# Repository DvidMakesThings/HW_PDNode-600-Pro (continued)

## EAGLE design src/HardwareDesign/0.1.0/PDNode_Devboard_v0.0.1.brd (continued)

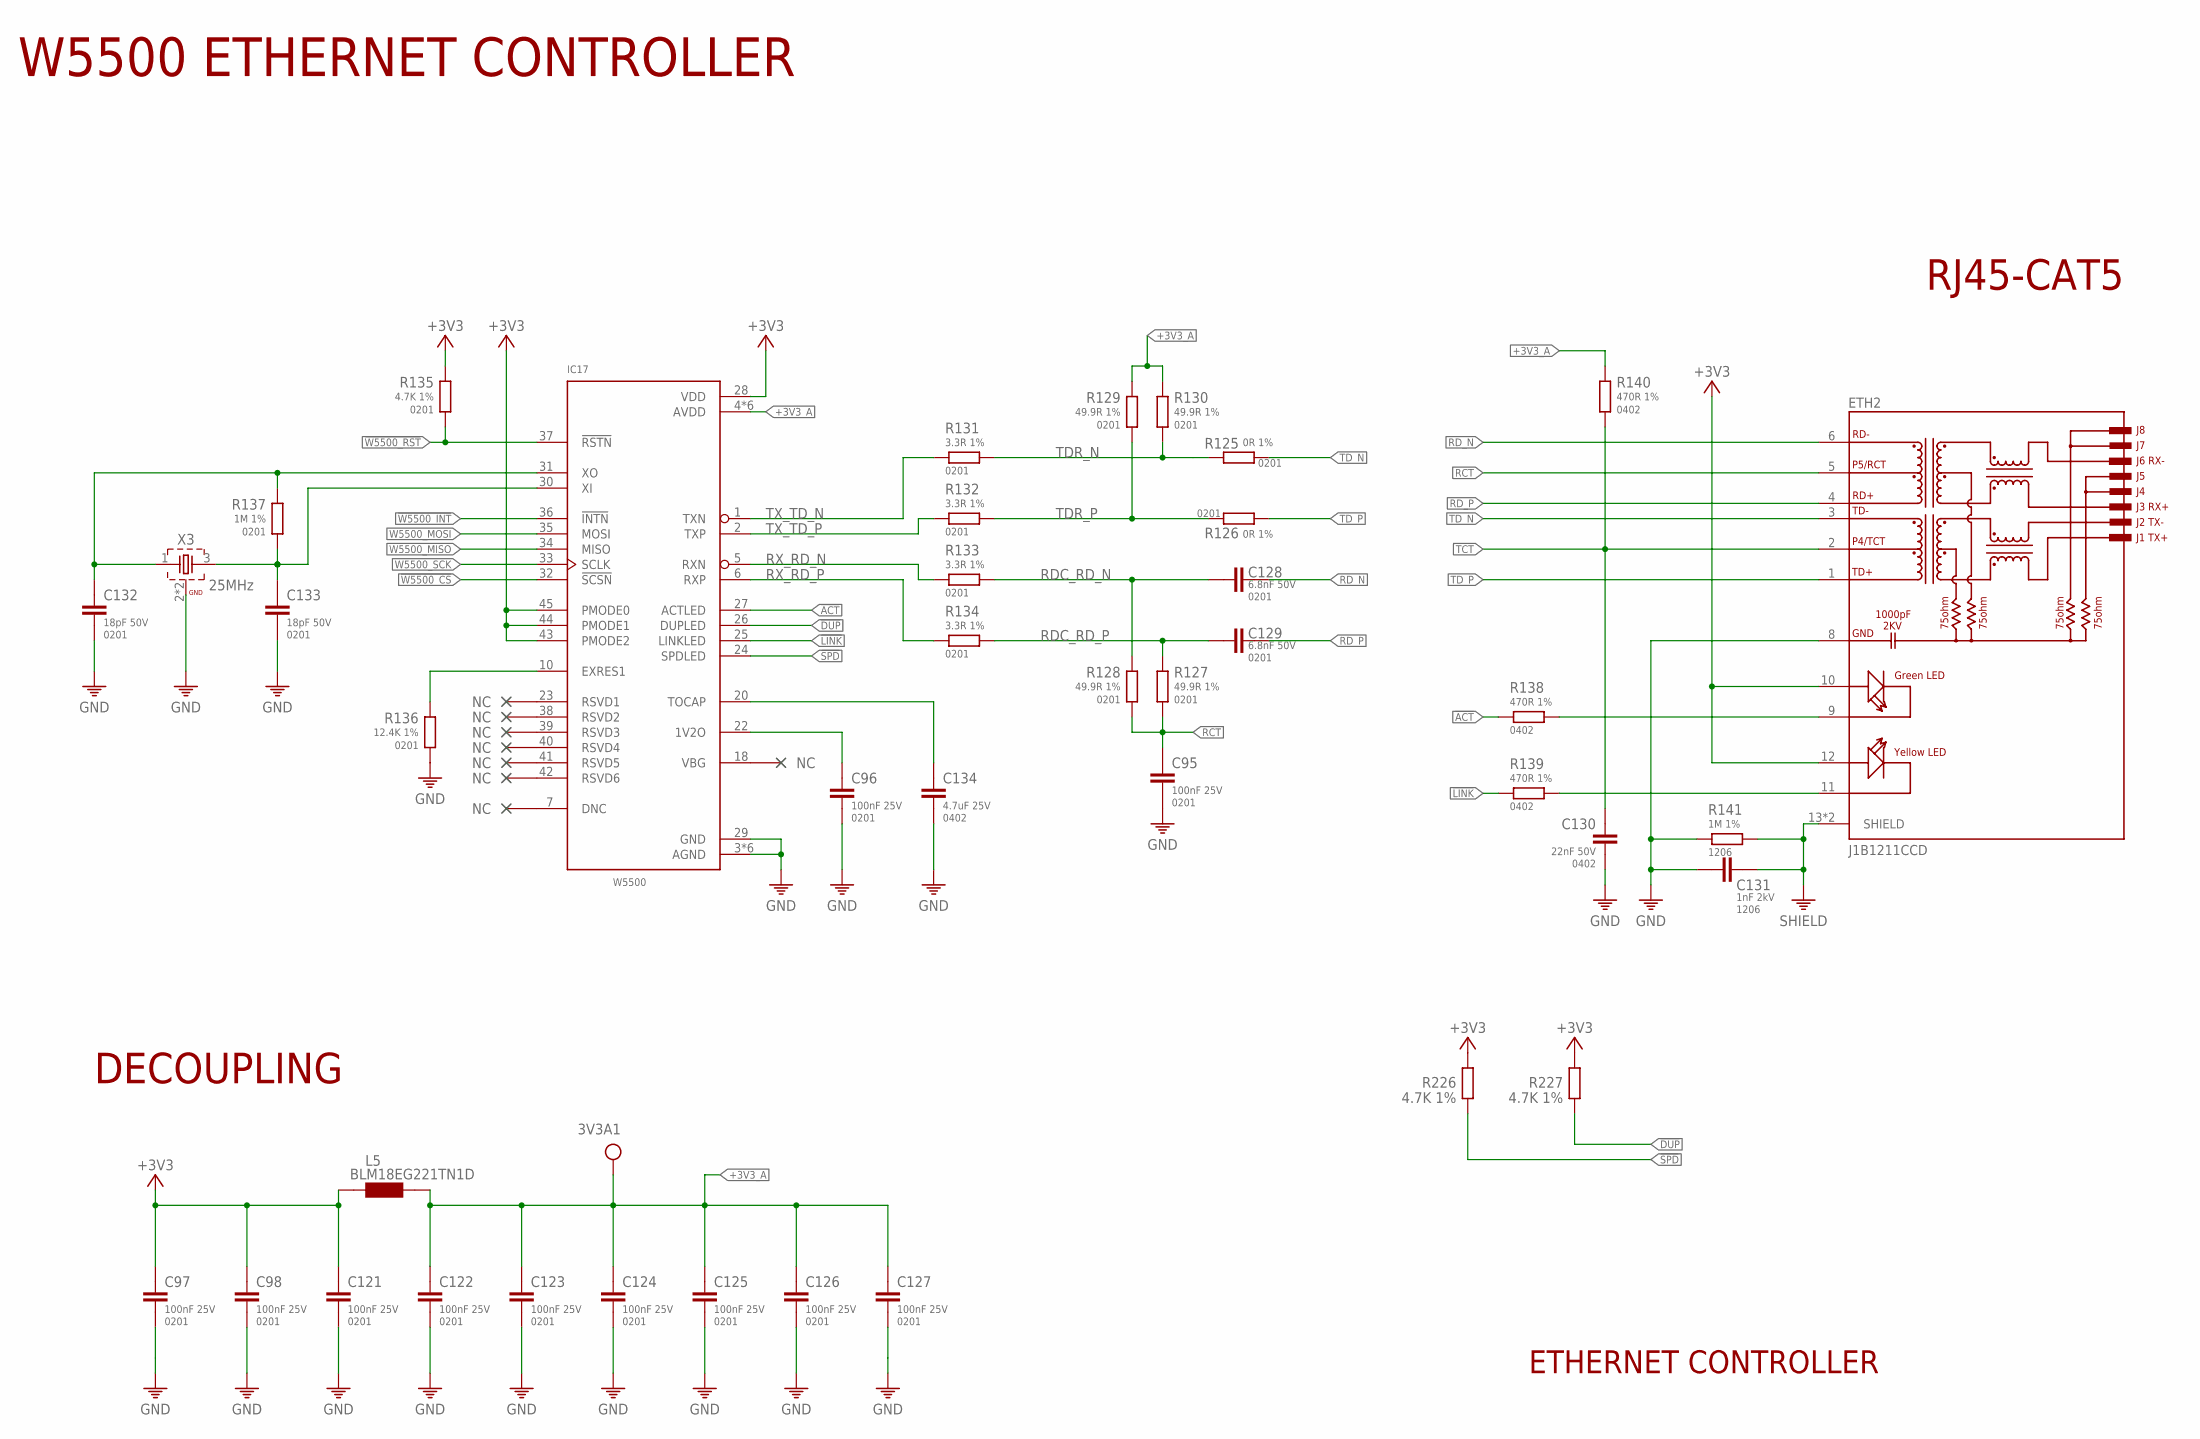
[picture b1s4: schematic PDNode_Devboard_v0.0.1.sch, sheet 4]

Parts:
3V3A1: DNI; TP-ROUND
C95, C96, C97, C98, C121, C122, C123, C124, C125, C126, C127: 100nF 25V; 0201
C128, C129: 6.8nF 50V; 0201
C130: 22nF 50V; 0402
C131: 1nF 2kV; 1206
C132, C133: 18pF 50V; 0201
C134: 4.7uF 25V; 0402
ETH2: J1B1211CCD
IC17: W5500; LQFP48
L5: BLM18EG221TN1D; 0603
R125, R126: 0R 1%; 0201
R127, R128, R129, R130: 49.9R 1%; 0201
R131, R132, R133, R134: 3.3R 1%; 0201
R135, R226, R227: 4.7K 1%; 0201
R136: 12.4K 1%; 0201
R137: 1M 1%; 0201
R138, R139, R140: 470R 1%; 0402
R141: 1M 1%; 1206
X3: 25MHz; WE-XTAL_CFPX-180

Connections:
!ACT: IC17.27 (ACTLED), R138.1
!DUP: IC17.26 (DUPLED), R227.1; also elsewhere on the board
!LINK: IC17.25 (LINKLED), R139.1
!SPD: IC17.24 (SPDLED), R226.1; also elsewhere on the board
!W5500_CS: IC17.32 (!SCSN); also elsewhere on the board
!W5500_INT: IC17.36 (!INTN); also elsewhere on the board
!W5500_RST: IC17.37 (!RSTN), R135.2; also elsewhere on the board
+3V3: C97.1, C98.1, C121.1, ETH2.10 (GREEN+), ETH2.12 (YELLOW+), IC17.28 (VDD), IC17.43 (PMODE2), IC17.44 (PMODE1), IC17.45 (PMODE0), L5.1, R135.1, R226.2, R227.2; also elsewhere on the board
+3V3_A: 3V3A1.TP, C122.1, C123.1, C124.1, C125.1, C126.1, C127.1, IC17.4 (AVDD), IC17.8 (AVDD), IC17.11 (AVDD), IC17.15 (AVDD), IC17.17 (AVDD), IC17.21 (AVDD), L5.2, R129.1, R130.1, R140.1
GND: C95.2, C96.2, C97.2, C98.2, C121.2, C122.2, C123.2, C124.2, C125.2, C126.2, C127.2, C130.2, C131.2, C132.2, C133.2, C134.2, ETH2.8 (GND), IC17.3 (AGND), IC17.9 (AGND), IC17.14 (AGND), IC17.16 (AGND), IC17.19 (AGND), IC17.29 (GND), IC17.48 (AGND), R136.2, R141.1, X3.2 (GND), X3.4 (GND); also elsewhere on the board
unnamed: ETH2.11 (YELLOW-), R139.2
unnamed: ETH2.9 (GREEN-), R138.2
unnamed: IC17.10 (EXRES1), R136.1
unnamed: C96.1, IC17.22 (1V2O)
unnamed: C134.1, IC17.20 (TOCAP)
unnamed: C133.1, IC17.30 (XI), R137.2, X3.3 (2)
RCT: C95.1, ETH2.5 (P5/RCT), R127.2, R128.2
RDC_RD_N: C128.1, R128.1, R133.2
RDC_RD_P: C129.1, R127.1, R134.2
RD_N: C128.2, ETH2.6 (RD-)
RD_P: C129.2, ETH2.4 (RD+)
RX_RD_N: IC17.5 (RXN), R133.1
RX_RD_P: IC17.6 (RXP), R134.1
SHIELD: C131.1, ETH2.13 (SHIELD), ETH2.14 (SHIELD), R141.2; also elsewhere on the board
TCT: C130.1, ETH2.2 (P4/TCT), R140.2
TDR_N: R125.1, R130.2, R131.2
TDR_P: R126.1, R129.2, R132.2
TD_N: ETH2.3 (TD-), R125.2
TD_P: ETH2.1 (TD+), R126.2
TX_TD_N: IC17.1 (TXN), R131.1
TX_TD_P: IC17.2 (TXP), R132.1
W5500_MISO: IC17.34 (MISO); also elsewhere on the board
W5500_MOSI: IC17.35 (MOSI); also elsewhere on the board
W5500_SCK: IC17.33 (SCLK); also elsewhere on the board
XO1: C132.1, IC17.31 (XO), R137.1, X3.1

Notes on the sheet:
W5500 ETHERNET CONTROLLER
ETHERNET CONTROLLER
RJ45-CAT5
DECOUPLING

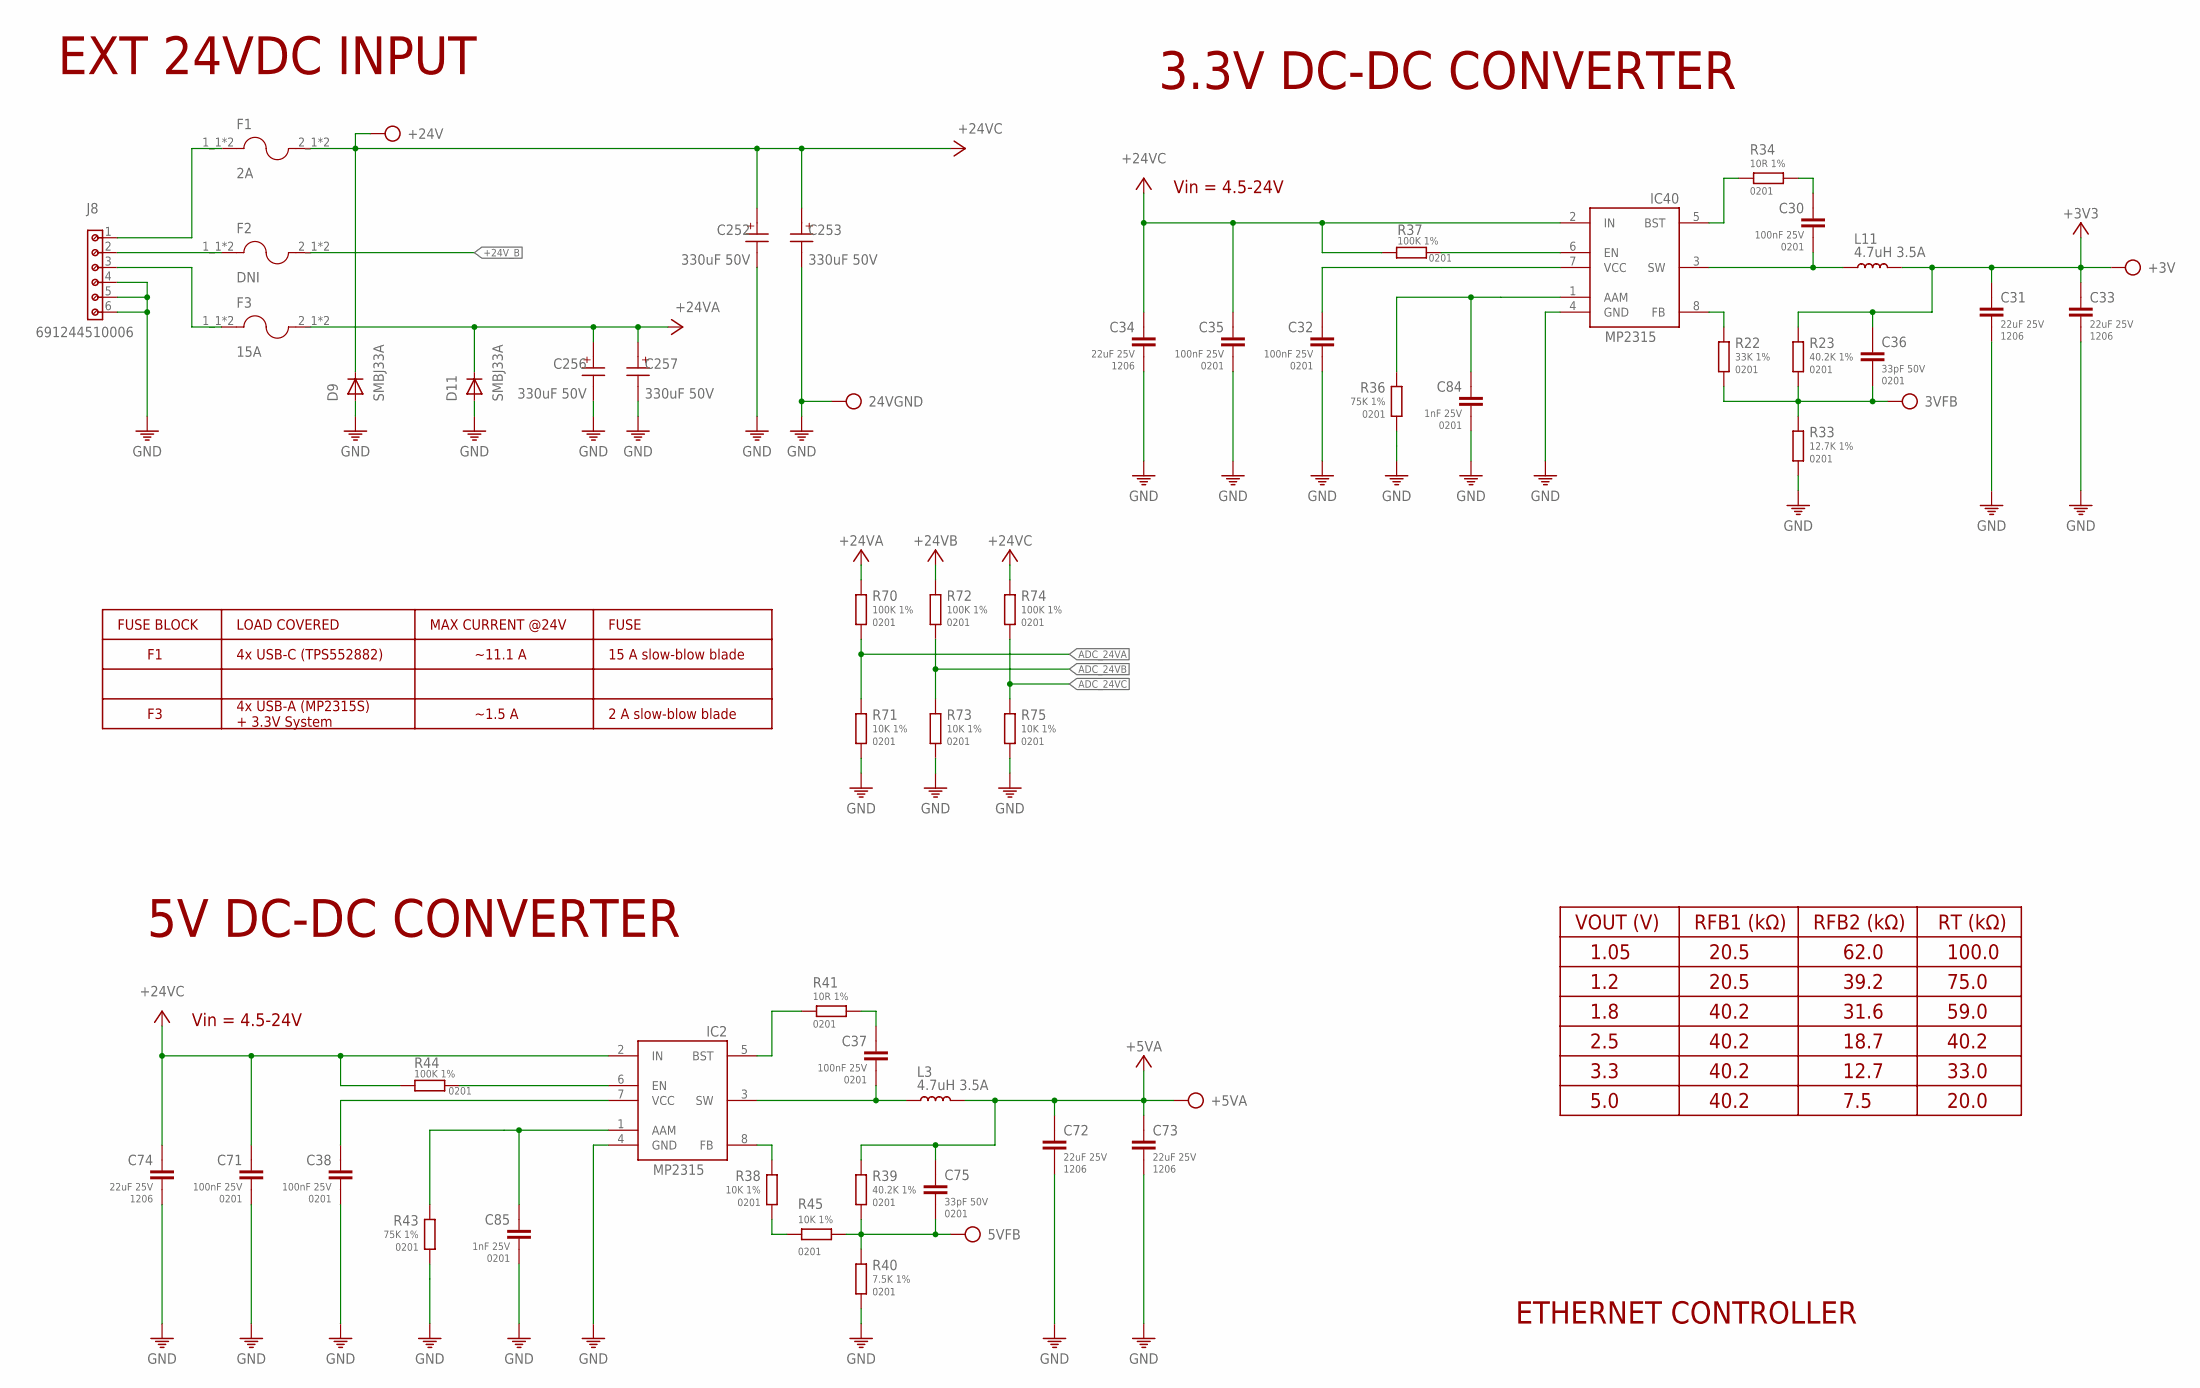
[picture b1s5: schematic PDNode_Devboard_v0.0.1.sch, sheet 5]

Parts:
3VFB, 5VFB, 24VGND: DNI; TP-ROUND
+3V, +5VA, +24V: DNI; TP-ROUND
C30, C32, C35, C37, C38, C71: 100nF 25V; 0201
C31, C33, C34, C72, C73, C74: 22uF 25V; 1206
C36, C75: 33pF 50V; 0201
C84, C85: 1nF 25V; 0201
C252, C253, C256, C257: 330uF 50V; 10X10.5(DXL)
D9, D11: SMBJ33A; SMB
F1: 2A; FUSE_3544-2
F2: DNI; FUSE_3544-2
F3: 15A; FUSE_3544-2
IC2, IC40: MP2315GJ-Z; SOT65P280X110-8N
J8: 691244510006
L3, L11: 4.7uH 3.5A; SRR5228A
R22: 33K 1%; 0201
R23, R39: 40.2K 1%; 0201
R33: 12.7K 1%; 0201
R34, R41: 10R 1%; 0201
R36, R43: 75K 1%; 0201
R37, R44, R70, R72, R74: 100K 1%; 0201
R38, R45, R71, R73, R75: 10K 1%; 0201
R40: 7.5K 1%; 0201

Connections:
3V3_EN_SYS1: IC40.6 (EN), R37.2
3V3_EN_SYS2: IC2.6 (EN), R44.2
24VINA: F3.1_1 (1), F3.1_2 (1), J8.3
24VINC: F1.1_1 (1), F1.1_2 (1), J8.1
+3V3: +3V.TP, C31.1, C33.1, C36.1, L11.2, R23.1; also elsewhere on the board
+5VA: +5VA.TP, C72.1, C73.1, C75.1, L3.2, R39.1; also elsewhere on the board
+24V_A: C256.1 (+), C257.1 (+), D11.C, F3.2_1 (2), F3.2_2 (2), R70.1; also elsewhere on the board
+24V_B: F2.2_1 (2), F2.2_2 (2), R72.1
+24V_C: +24V.TP, C34.1, C35.1, C71.1, C74.1, C252.1 (+), C253.1 (+), D9.C, F1.2_1 (2), F1.2_2 (2), IC2.2 (IN), IC40.2 (IN), R37.1, R44.1, R74.1
ADC_24VA: R70.2, R71.1; also elsewhere on the board
ADC_24VB: R72.2, R73.1; also elsewhere on the board
ADC_24VC: R74.2, R75.1; also elsewhere on the board
GND: 24VGND.TP, C31.2, C32.2, C33.2, C34.2, C35.2, C38.2, C71.2, C72.2, C73.2, C74.2, C84.2, C85.2, C252.2 (-), C253.2 (-), C256.2 (-), C257.2 (-), D9.A, D11.A, IC2.4 (GND), IC40.4 (GND), J8.4, J8.5, J8.6, R33.2, R36.2, R40.2, R43.2, R71.2, R73.2, R75.2; also elsewhere on the board
unnamed: IC2.5 (BST), R41.1
unnamed: IC2.8 (FB), R38.1
unnamed: C37.1, R41.2
unnamed: 5VFB.TP, C75.2, R39.2, R40.1, R45.2
unnamed: C38.1, IC2.7 (VCC)
unnamed: C85.1, IC2.1 (AAM), R43.1
unnamed: R38.2, R45.1
unnamed: F2.1_1 (1), F2.1_2 (1), J8.2
unnamed: IC40.5 (BST), R34.1
unnamed: IC40.8 (FB), R22.1
unnamed: C30.1, R34.2
unnamed: 3VFB.TP, C36.2, R22.2, R23.2, R33.1
unnamed: C32.1, IC40.7 (VCC)
unnamed: C84.1, IC40.1 (AAM), R36.1
SW1: C37.2, IC2.3 (SW), L3.1
SW3: C30.2, IC40.3 (SW), L11.1

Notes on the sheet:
VOUT (V)
EXT 24VDC INPUT
FUSE BLOCK
LOAD COVERED
MAX CURRENT @24V
FUSE
4x USB-C (TPS552882)
4x USB-A (MP2315S) + 3.3V System
~11.1 A
~1.5 A
15 A slow-blow blade
2 A slow-blow blade
RFB1 (kΩ)
RFB2 (kΩ)
RT (kΩ)
1.05
1.2
1.8
3.3
5.0
20.5
40.2
62.0
39.2
31.6
18.7
12.7
7.5
2.5
100.0
75.0
59.0
33.0
20.0
3.3V DC-DC CONVERTER
Vin = 4.5-24V
5V DC-DC CONVERTER
ETHERNET CONTROLLER

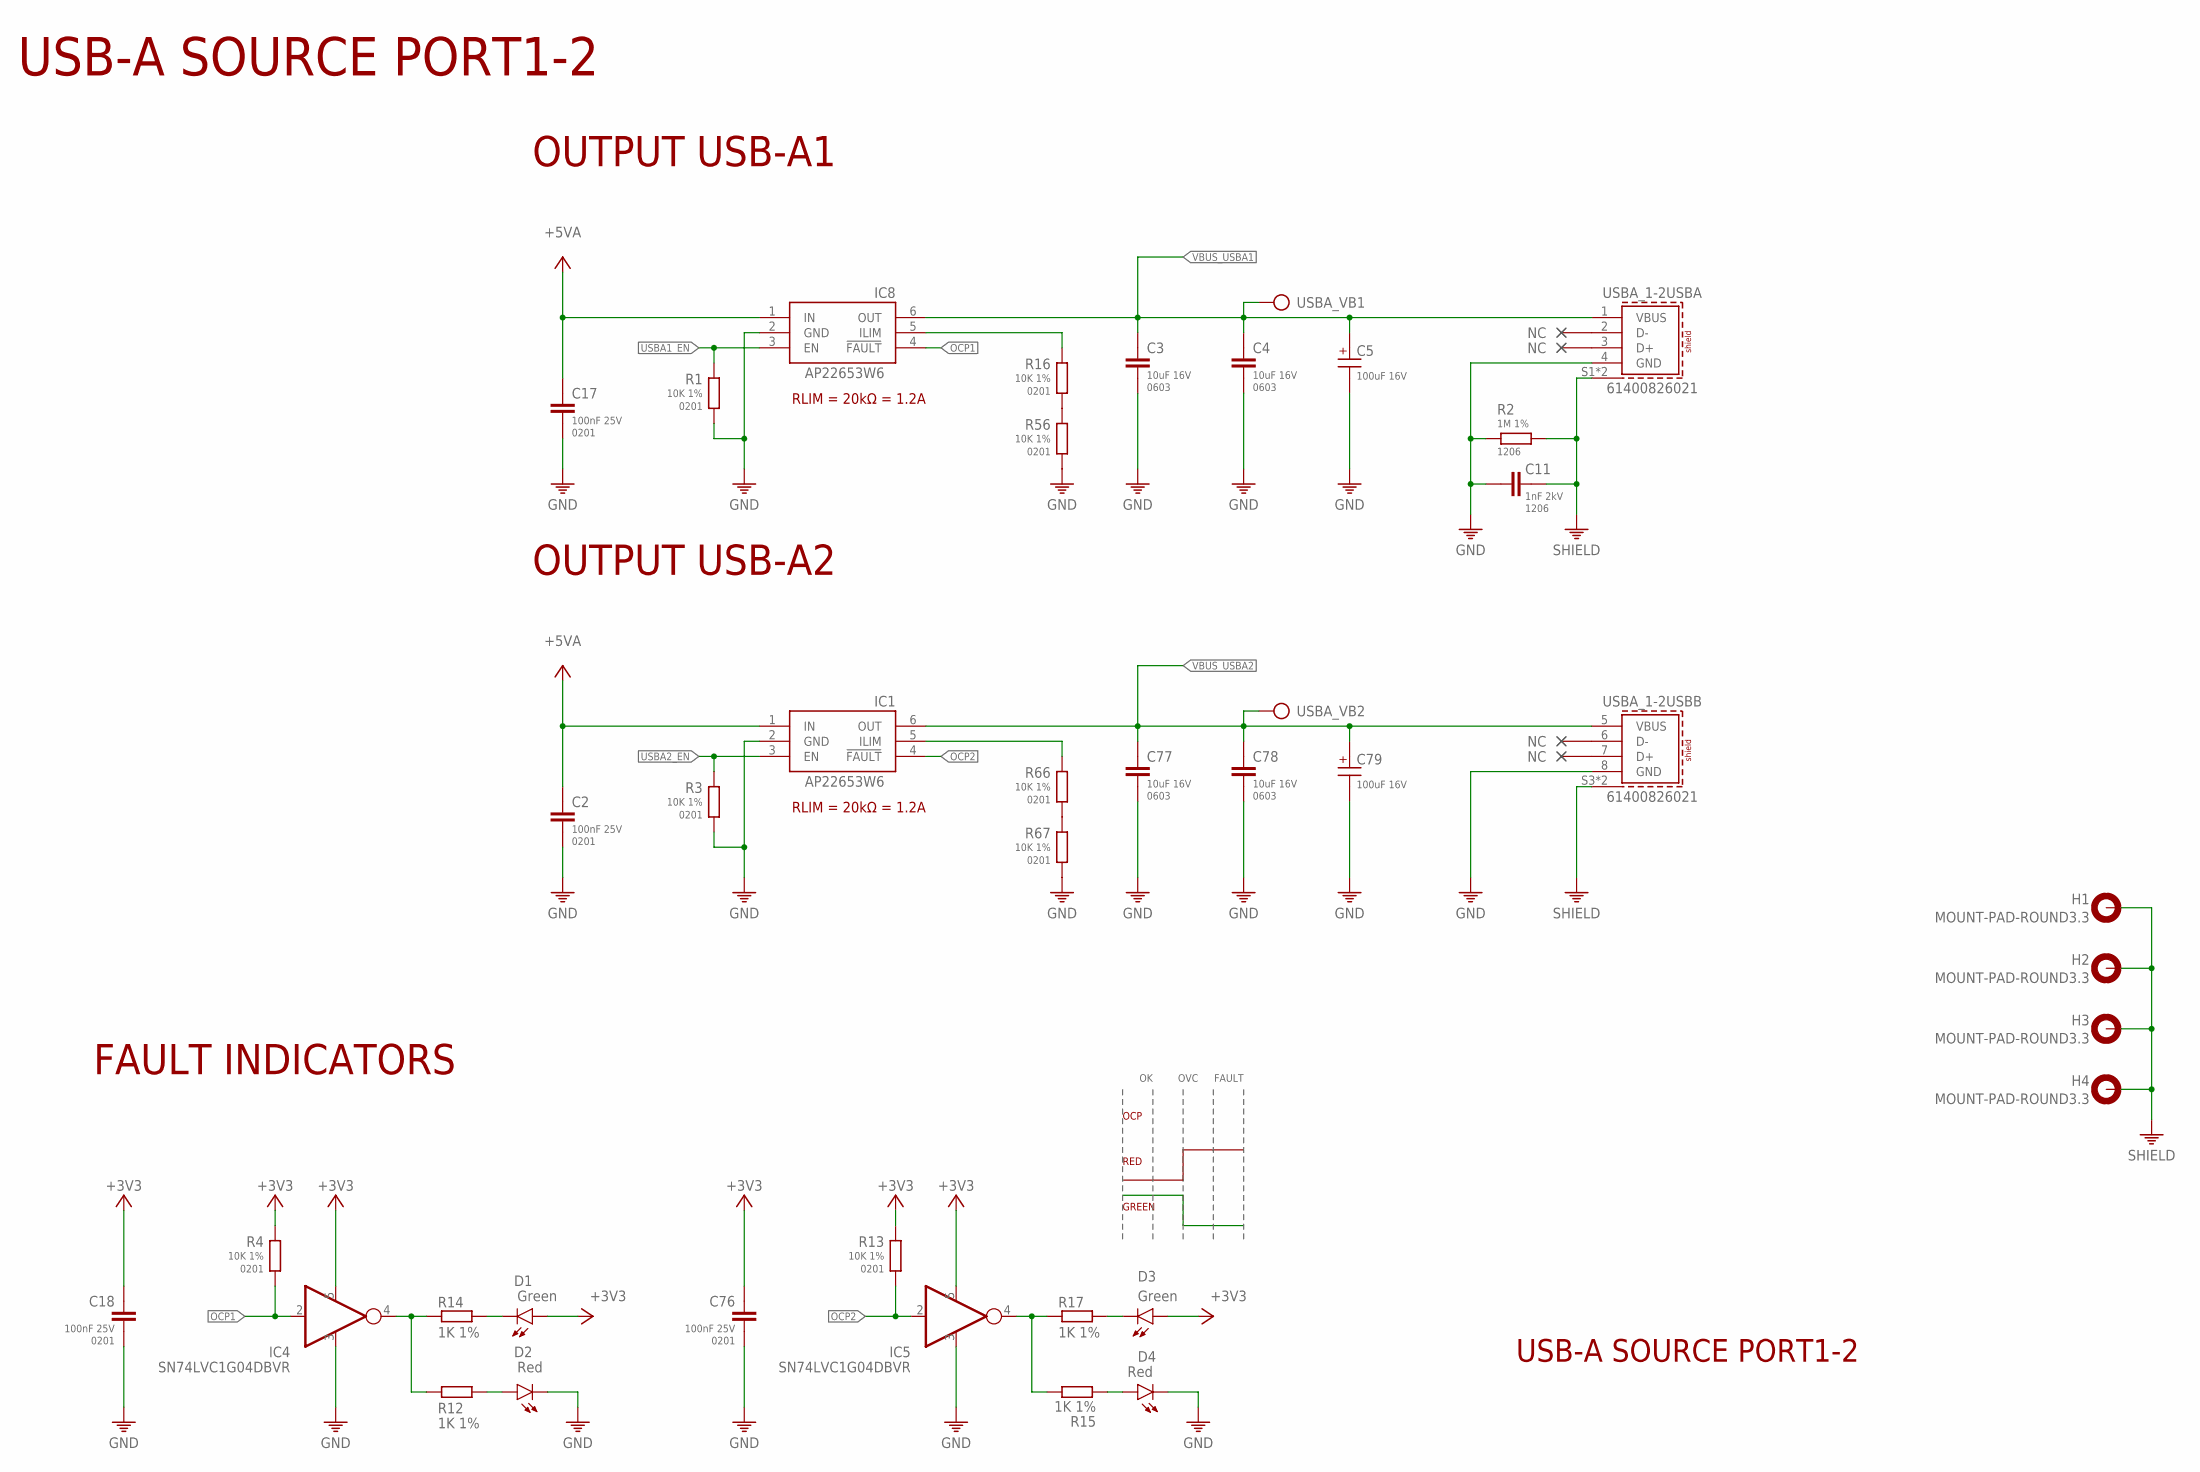
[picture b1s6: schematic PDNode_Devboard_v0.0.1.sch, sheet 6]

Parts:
C2, C17, C18, C76: 100nF 25V; 0201
C3, C4, C77, C78: 10uF 16V; 0603
C5, C79: 100uF 16V; 5X5.5(DXL)
C11: 1nF 2kV; 1206
D1, D3: Green; LED-0603
D2, D4: Red; LED-0603
H1, H2, H3, H4: MOUNT-PAD-ROUND3.3; 3,3-PAD
IC1, IC8: AP22653W6; SOT23-6
IC4, IC5: SN74LVC1G04DBVR; SOT95P280X145-5N
R1, R3, R4, R13, R16, R56, R66, R67: 10K 1%; 0201
R2: 1M 1%; 1206
R12, R14, R15, R17: 1K 1%; 0402
USBA_1-2: 61400826021
USBA_VB1, USBA_VB2: DNI; TP-ROUND

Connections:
+3V3: C18.1, C76.1, D1.A, D3.A, IC4.5 (V+), IC5.5 (V+), R4.1, R13.1; also elsewhere on the board
+5VA: C2.1, C17.1, IC1.1 (IN), IC8.1 (IN); also elsewhere on the board
GND: C2.2, C3.2, C4.2, C5.2 (-), C11.2, C17.2, C18.2, C76.2, C77.2, C78.2, C79.2 (-), D2.C, D4.C, IC1.2 (GND), IC4.3 (V-), IC5.3 (V-), IC8.2 (GND), R1.2, R2.1, R3.2, R56.2, R67.2, USBA_1-2.4 (GND), USBA_1-2.8 (GND); also elsewhere on the board
unnamed: IC1.5 (ILIM), R66.1
unnamed: D2.A, R12.2
unnamed: IC4.4 (OUT), R12.1, R14.1
unnamed: D1.C, R14.2
unnamed: D4.A, R15.1
unnamed: IC5.4 (OUT), R15.2, R17.1
unnamed: D3.C, R17.2
unnamed: R16.2, R56.1
unnamed: R66.2, R67.1
unnamed: IC8.5 (ILIM), R16.1
OCP1: IC4.2 (IN), IC8.4 (!FAULT), R4.2; also elsewhere on the board
OCP2: IC1.4 (!FAULT), IC5.2 (IN), R13.2; also elsewhere on the board
SHIELD: C11.1, H1.B3,3, H2.B3,3, H3.B3,3, H4.B3,3, R2.2, USBA_1-2.S1 (SHIELD), USBA_1-2.S2 (SHIELD), USBA_1-2.S3 (SHIELD), USBA_1-2.S4 (SHIELD); also elsewhere on the board
USBA1_EN: IC8.3 (EN), R1.1; also elsewhere on the board
USBA2_EN: IC1.3 (EN), R3.1; also elsewhere on the board
VBUS_USBA1: C3.1, C4.1, C5.1 (+), IC8.6 (OUT), USBA_1-2.1 (VBUS), USBA_VB1.TP
VBUS_USBA2: C77.1, C78.1, C79.1 (+), IC1.6 (OUT), USBA_1-2.5 (VBUS), USBA_VB2.TP

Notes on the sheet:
OUTPUT USB-A1
RLIM = 20kΩ = 1.2A
OUTPUT USB-A2
FAULT INDICATORS
USB-A SOURCE PORT1-2
OCP
RED
GREEN
OVC
FAULT

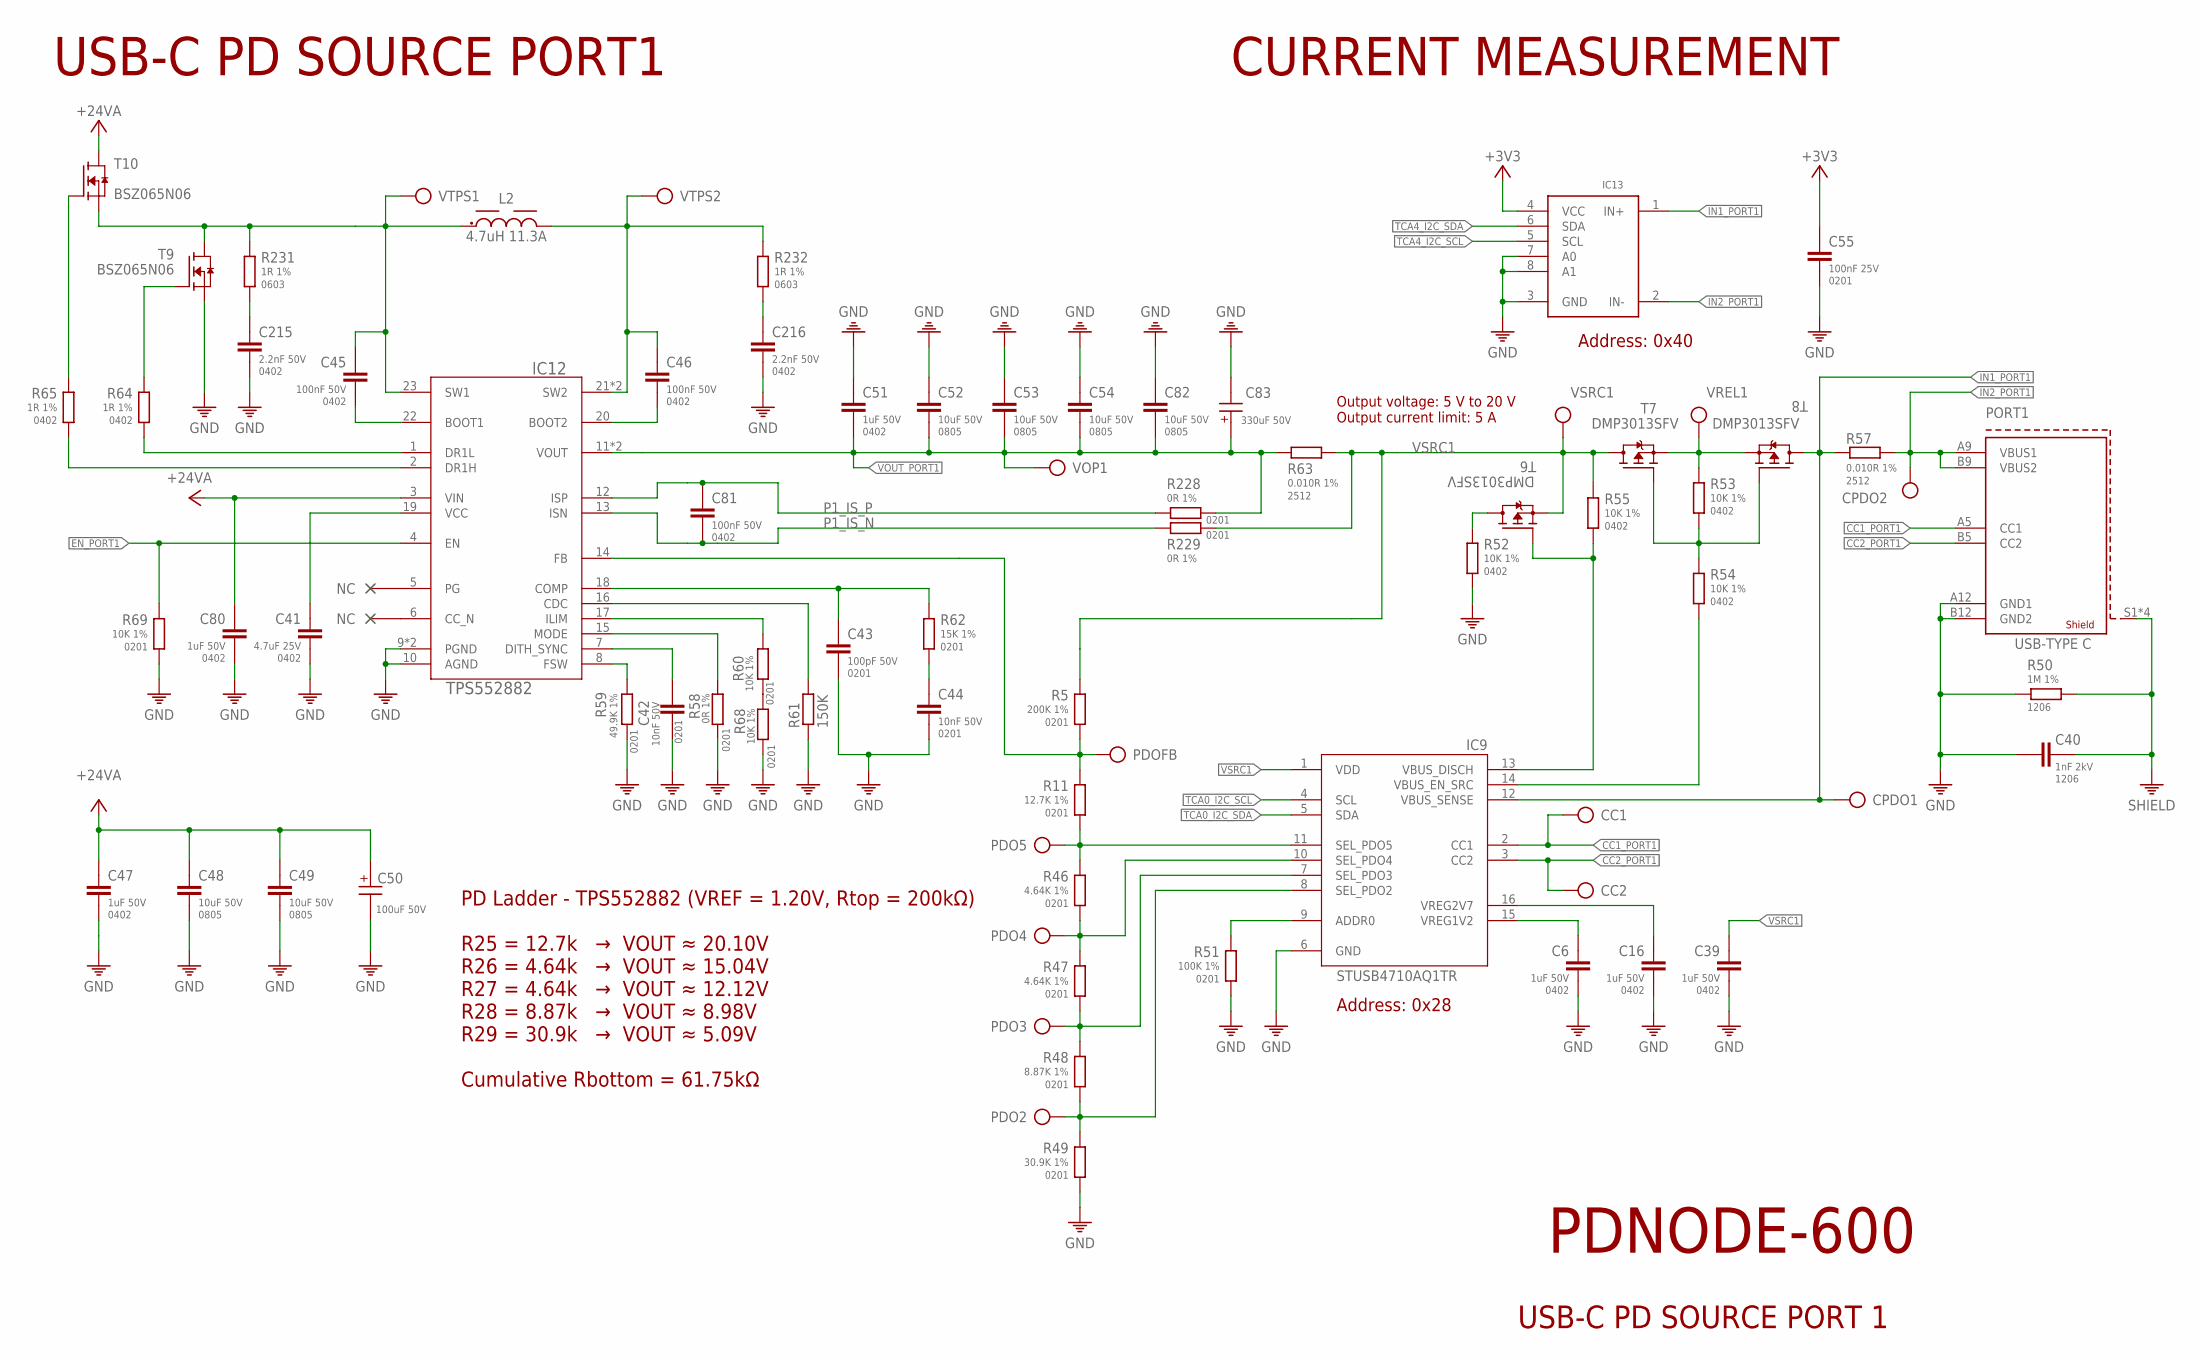
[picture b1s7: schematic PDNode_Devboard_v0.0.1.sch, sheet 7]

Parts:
C6, C16, C39, C47, C51, C80: 1uF 50V; 0402
C40: 1nF 2kV; 1206
C41: 4.7uF 25V; 0402
C42, C44: 10nF 50V; 0201
C43: 100pF 50V; 0201
C45, C46, C81: 100nF 50V; 0402
C48, C49, C52, C53, C54, C82: 10uF 50V; 0805
C50: 100uF 50V; 6.3X7.7(DXL)
C55: 100nF 25V; 0201
C83: 330uF 50V; 10X10.5(DXL)
C215, C216: 2.2nF 50V; 0402
CC1, CC2: DNI; TP-ROUND
CPDO1, CPDO2: DNI; TP-ROUND
IC9: STUSB4710AQ1TR; QFN50P300X300X55-16N
IC12: TPS552882; RPM0026A-MFG
IC13: INA219BIDCNT; SOT23-8
L2: 4.7uH 11.3A; WE-PDHV_1280
PDO2, PDO3, PDO4, PDO5: DNI; TP-ROUND
PDOFB: DNI; TP-ROUND
PORT1: 632722100213
R5: 200K 1%; 0201
R11: 12.7K 1%; 0201
R46, R47: 4.64K 1%; 0201
R48: 8.87K 1%; 0201
R49: 30.9K 1%; 0201
R50: 1M 1%; 1206
R51: 100K 1%; 0201
R52, R53, R54, R55: 10K 1%; 0402
R57, R63: 0.010R 1%; 2512
R58, R228, R229: 0R 1%; 0201
R59: 49.9K 1%; 0201
R60, R68, R69: 10K 1%; 0201
R61: 150K; R0201
R62: 15K 1%; 0201
R64, R65: 1R 1%; 0402
R231, R232: 1R 1%; 0603
T6, T7, T8: DMP3013SFV; POWERDI3333-8_UX_DIO-L
T9, T10: BSZ065N06; POWERDI3333-8_UX_DIO-L
VOP1: DNI; TP-ROUND
VREL1: DNI; TP-ROUND
VSRC1: DNI; TP-ROUND
VTPS1, VTPS2: DNI; TP-ROUND

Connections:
+3V3: C55.1, IC13.4 (VCC); also elsewhere on the board
+24V_A: C47.1, C48.1, C49.1, C50.1 (+), C80.1, IC12.3 (VIN), T10.5 (D), T10.6 (D), T10.7 (D), T10.8 (D), T10.9 (D); also elsewhere on the board
CC1_PORT1: CC1.TP, IC9.2 (CC1), PORT1.A5 (CC1)
CC2_PORT1: CC2.TP, IC9.3 (CC2), PORT1.B5 (CC2)
DISCHARGE1: R52.1, T6.5 (D), T6.6 (D), T6.7 (D), T6.8 (D), T6.9 (D)
EN_PORT1: IC12.4 (EN), R69.1; also elsewhere on the board
GND: C6.2, C16.2, C39.2, C40.1, C41.2, C42.2, C43.2, C44.2, C47.2, C48.2, C49.2, C50.2 (-), C51.1, C52.1, C53.1, C54.1, C55.2, C80.2, C82.1, C83.2 (-), C215.2, C216.2, IC9.6 (GND), IC12.9 (PGND), IC12.10 (AGND), IC12.24 (PGND), IC13.3 (GND), IC13.7 (A0), IC13.8 (A1), PORT1.A12 (GND1), PORT1.B12 (GND2), R49.2, R50.1, R51.2, R52.2, R58.2, R59.2, R61.2, R68.2, R69.2, T9.1 (S), T9.2 (S), T9.3 (S); also elsewhere on the board
IN1_PORT1: CPDO1.TP, IC9.12 (VBUS_SENSE), IC13.1 (IN+), R57.2, T8.5 (D), T8.6 (D), T8.7 (D), T8.8 (D), T8.9 (D)
IN2_PORT1: CPDO2.TP, IC13.2 (IN-), PORT1.A9 (VBUS1), PORT1.B9 (VBUS2), R57.1
IND1: C45.1, IC12.23 (SW1), L2.1, R231.1, T9.5 (D), T9.6 (D), T9.7 (D), T9.8 (D), T9.9 (D), T10.1 (S), T10.2 (S), T10.3 (S), VTPS1.TP
INDOUT1: C46.1, IC12.21 (SW2), IC12.25 (SW2), L2.2, R232.1, VTPS2.TP
unnamed: R60.2, R68.1
unnamed: IC12.14 (FB), PDOFB.TP, R5.2, R11.1
unnamed: C215.1, R231.2
unnamed: C216.1, R232.2
unnamed: IC9.11 (SEL_PDO5), PDO5.TP, R11.2, R46.1
unnamed: IC9.10 (SEL_PDO4), PDO4.TP, R46.2, R47.1
unnamed: IC9.7 (SEL_PDO3), PDO3.TP, R47.2, R48.1
unnamed: IC9.8 (SEL_PDO2), PDO2.TP, R48.2, R49.1
unnamed: C6.1, IC9.15 (VREG1V2)
unnamed: C16.1, IC9.16 (VREG2V7)
unnamed: IC9.9 (ADDR0), R51.1
unnamed: IC9.13 (VBUS_DISCH), R55.2, T6.4 (G)
unnamed: R53.2, R54.1, T7.4 (G), T8.4 (G)
unnamed: IC9.14 (VBUS_EN_SRC), R54.2
unnamed: C44.1, R62.2
unnamed: IC12.8 (FSW), R59.1
unnamed: C42.1, IC12.7 (DITH_SYNC)
unnamed: IC12.15 (MODE), R58.1
unnamed: IC12.17 (ILIM), R60.1
unnamed: IC12.16 (CDC), R61.1
unnamed: C43.1, IC12.18 (COMP), R62.1
unnamed: C41.1, IC12.19 (VCC)
unnamed: C45.2, IC12.22 (BOOT1)
unnamed: C46.2, IC12.20 (BOOT2)
unnamed: R65.1, T10.4 (G)
unnamed: R64.1, T9.4 (G)
unnamed: IC12.1 (DR1L), R64.2
unnamed: IC12.2 (DR1H), R65.2
P1_IS_N: C81.2, IC12.13 (ISN), R229.1
P1_IS_P: C81.1, IC12.12 (ISP), R228.1
SHIELD: C40.2, PORT1.S1 (SHIELD1), PORT1.S2 (SHIELD1), PORT1.S3 (SHIELD1), PORT1.S4 (SHIELD1), R50.2; also elsewhere on the board
SOURCE1: R53.1, T7.1 (S), T7.2 (S), T7.3 (S), T8.1 (S), T8.2 (S), T8.3 (S), VREL1.TP
TCA0_I2C_SCL: IC9.4 (SCL); also elsewhere on the board
TCA0_I2C_SDA: IC9.5 (SDA); also elsewhere on the board
TCA4_I2C_SCL: IC13.5 (SCL); also elsewhere on the board
TCA4_I2C_SDA: IC13.6 (SDA); also elsewhere on the board
VOUT_PORT1: C51.2, C52.2, C53.2, C54.2, C82.2, C83.1 (+), IC12.11 (VOUT), IC12.26 (VOUT), R63.2, R228.2, VOP1.TP
VSRC1: C39.1, IC9.1 (VDD), R5.1, R55.1, R63.1, R229.2, T6.1 (S), T6.2 (S), T6.3 (S), T7.5 (D), T7.6 (D), T7.7 (D), T7.8 (D), T7.9 (D), VSRC1.TP

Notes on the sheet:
USB-C PD SOURCE PORT1
CURRENT MEASUREMENT
Output voltage: 5 V to 20 V Output current limit: 5 A
PD Ladder - TPS552882 (VREF = 1.20V, Rtop = 200kΩ) R25 = 12.7k → VOUT ≈ 20.10V R26 = 4.64k → VOUT ≈ 15.04V R27 = 4.64k → VOUT ≈ 12.12V R28 = 8.87k → VOUT ≈ 8.98V R29 = 30.9k → VOUT ≈ 5.09V Cumulative Rbottom = 61.75kΩ
Address: 0x40
Address: 0x28
USB-C PD SOURCE PORT 1
PDNODE-600

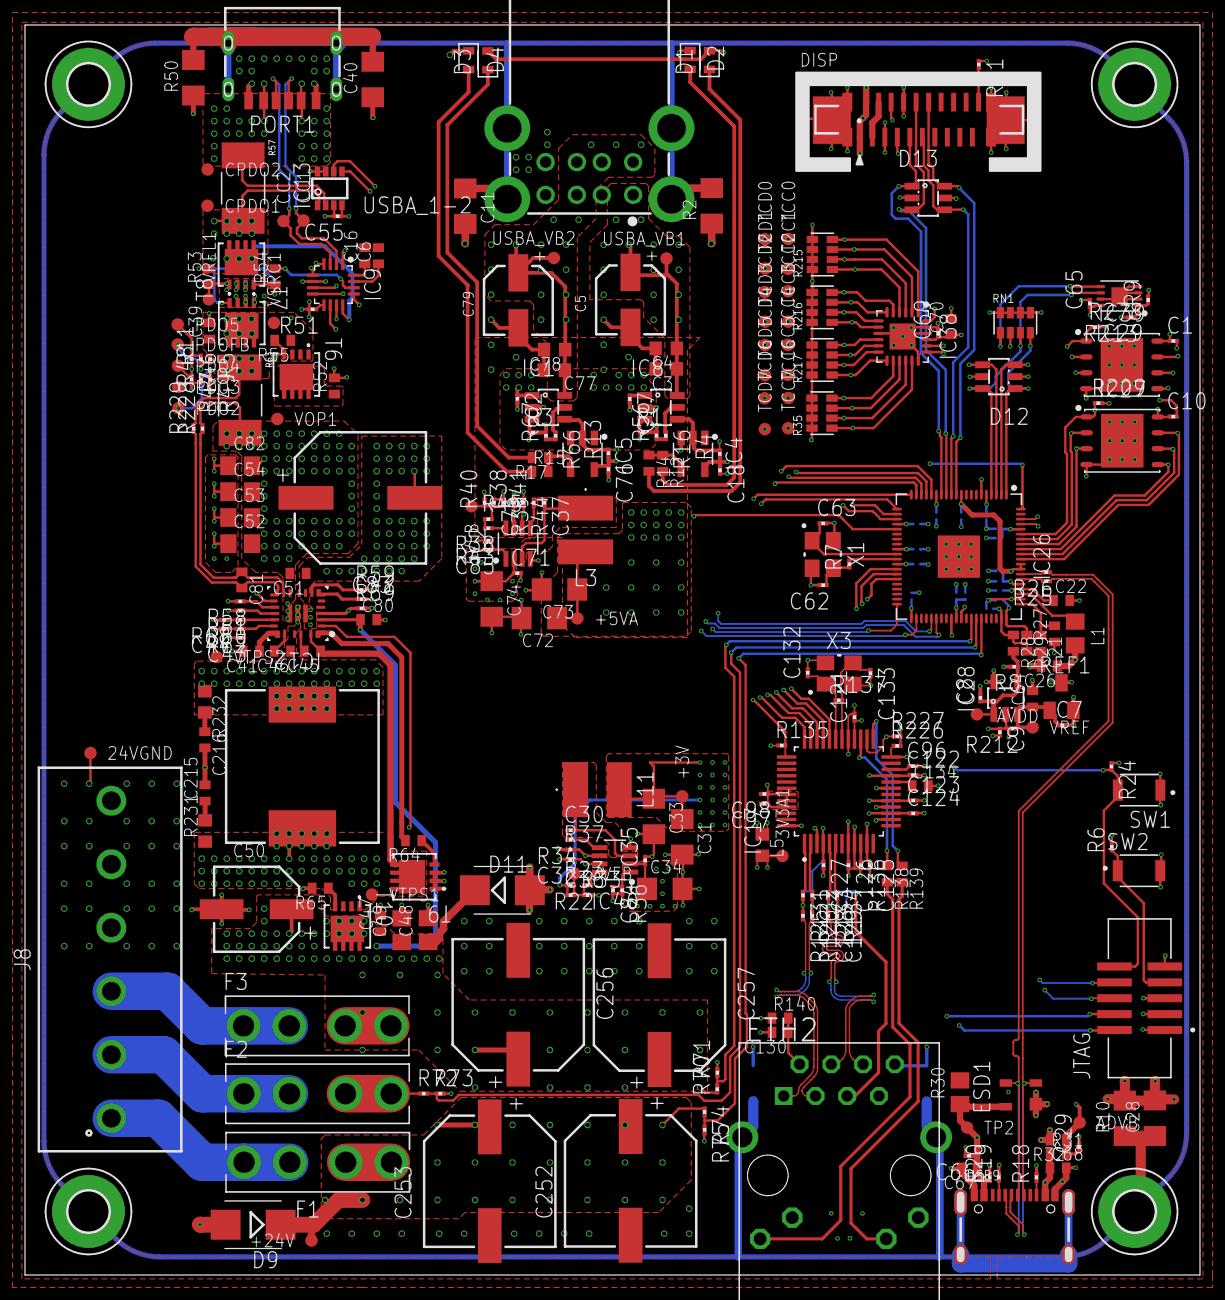
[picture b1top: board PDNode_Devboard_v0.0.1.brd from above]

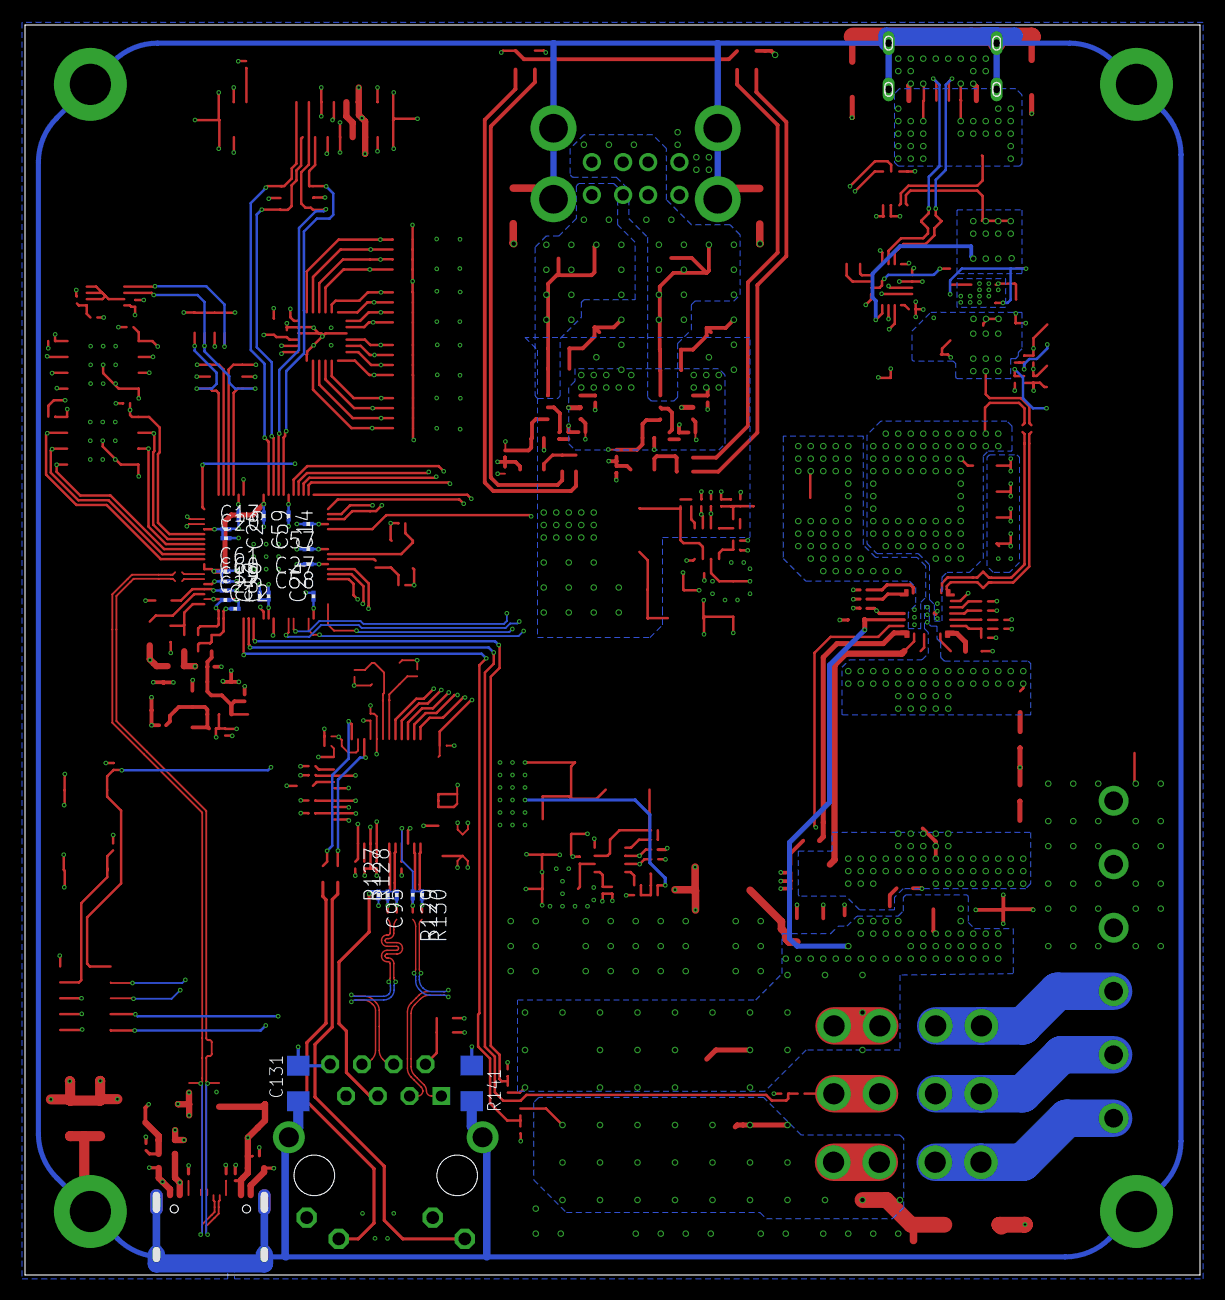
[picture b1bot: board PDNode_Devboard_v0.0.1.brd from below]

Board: 6 copper layers, 94.0 x 100.0 mm, 311 parts (23 on the bottom side), 177 nets.
